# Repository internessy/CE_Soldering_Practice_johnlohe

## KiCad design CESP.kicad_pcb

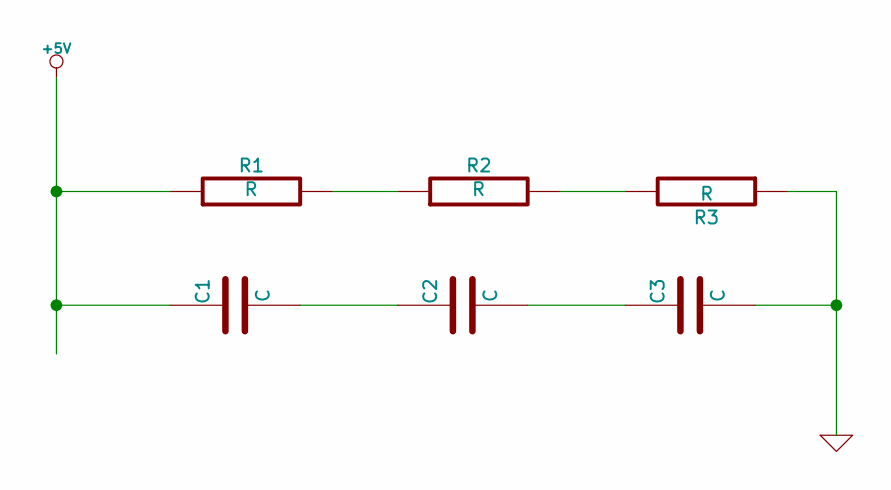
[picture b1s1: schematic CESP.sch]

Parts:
C1, C2, C3: C
R1, R2, R3: R

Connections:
+5V: C1.1, R1.1
GND: C3.2, R3.1
unnamed: C2.2, C3.1
unnamed: C1.2, C2.1
unnamed: R2.2, R3.2
unnamed: R1.2, R2.1

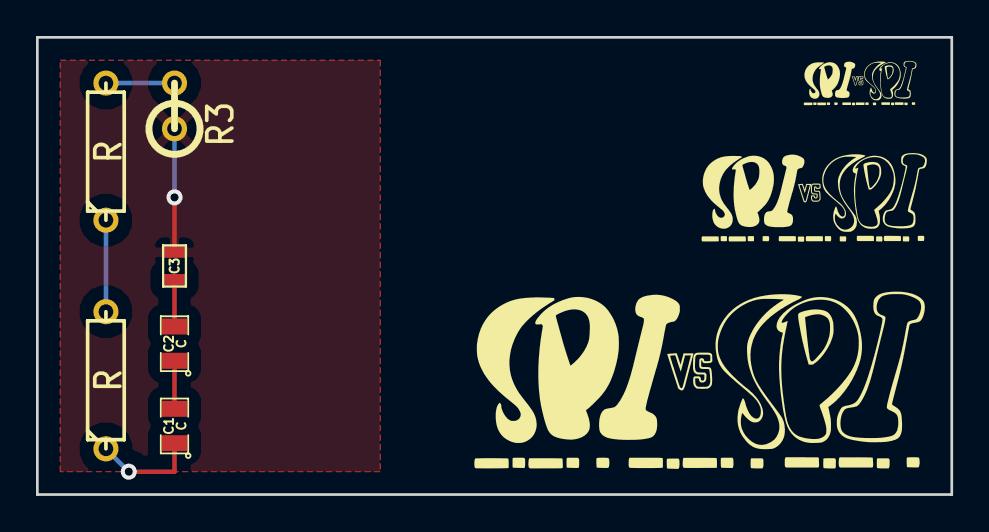
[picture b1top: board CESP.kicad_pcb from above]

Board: 2 copper layers, 50.8 x 25.4 mm, 9 parts (0 on the bottom side), 6 nets.

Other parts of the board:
VAL: SPIvsSPI_250
VAL#2: SPIvsSPI_1; SPIvsSPI_500
VAL#3: SPIvsSPI_1; SPIvsSPI_1000

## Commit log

2014-01-26 second commit
2014-01-26 third commit
2014-01-27 Added SPIvsSPI Library
